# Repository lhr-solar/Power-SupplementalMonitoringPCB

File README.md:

# Power-SupplementalMonitoringPCB

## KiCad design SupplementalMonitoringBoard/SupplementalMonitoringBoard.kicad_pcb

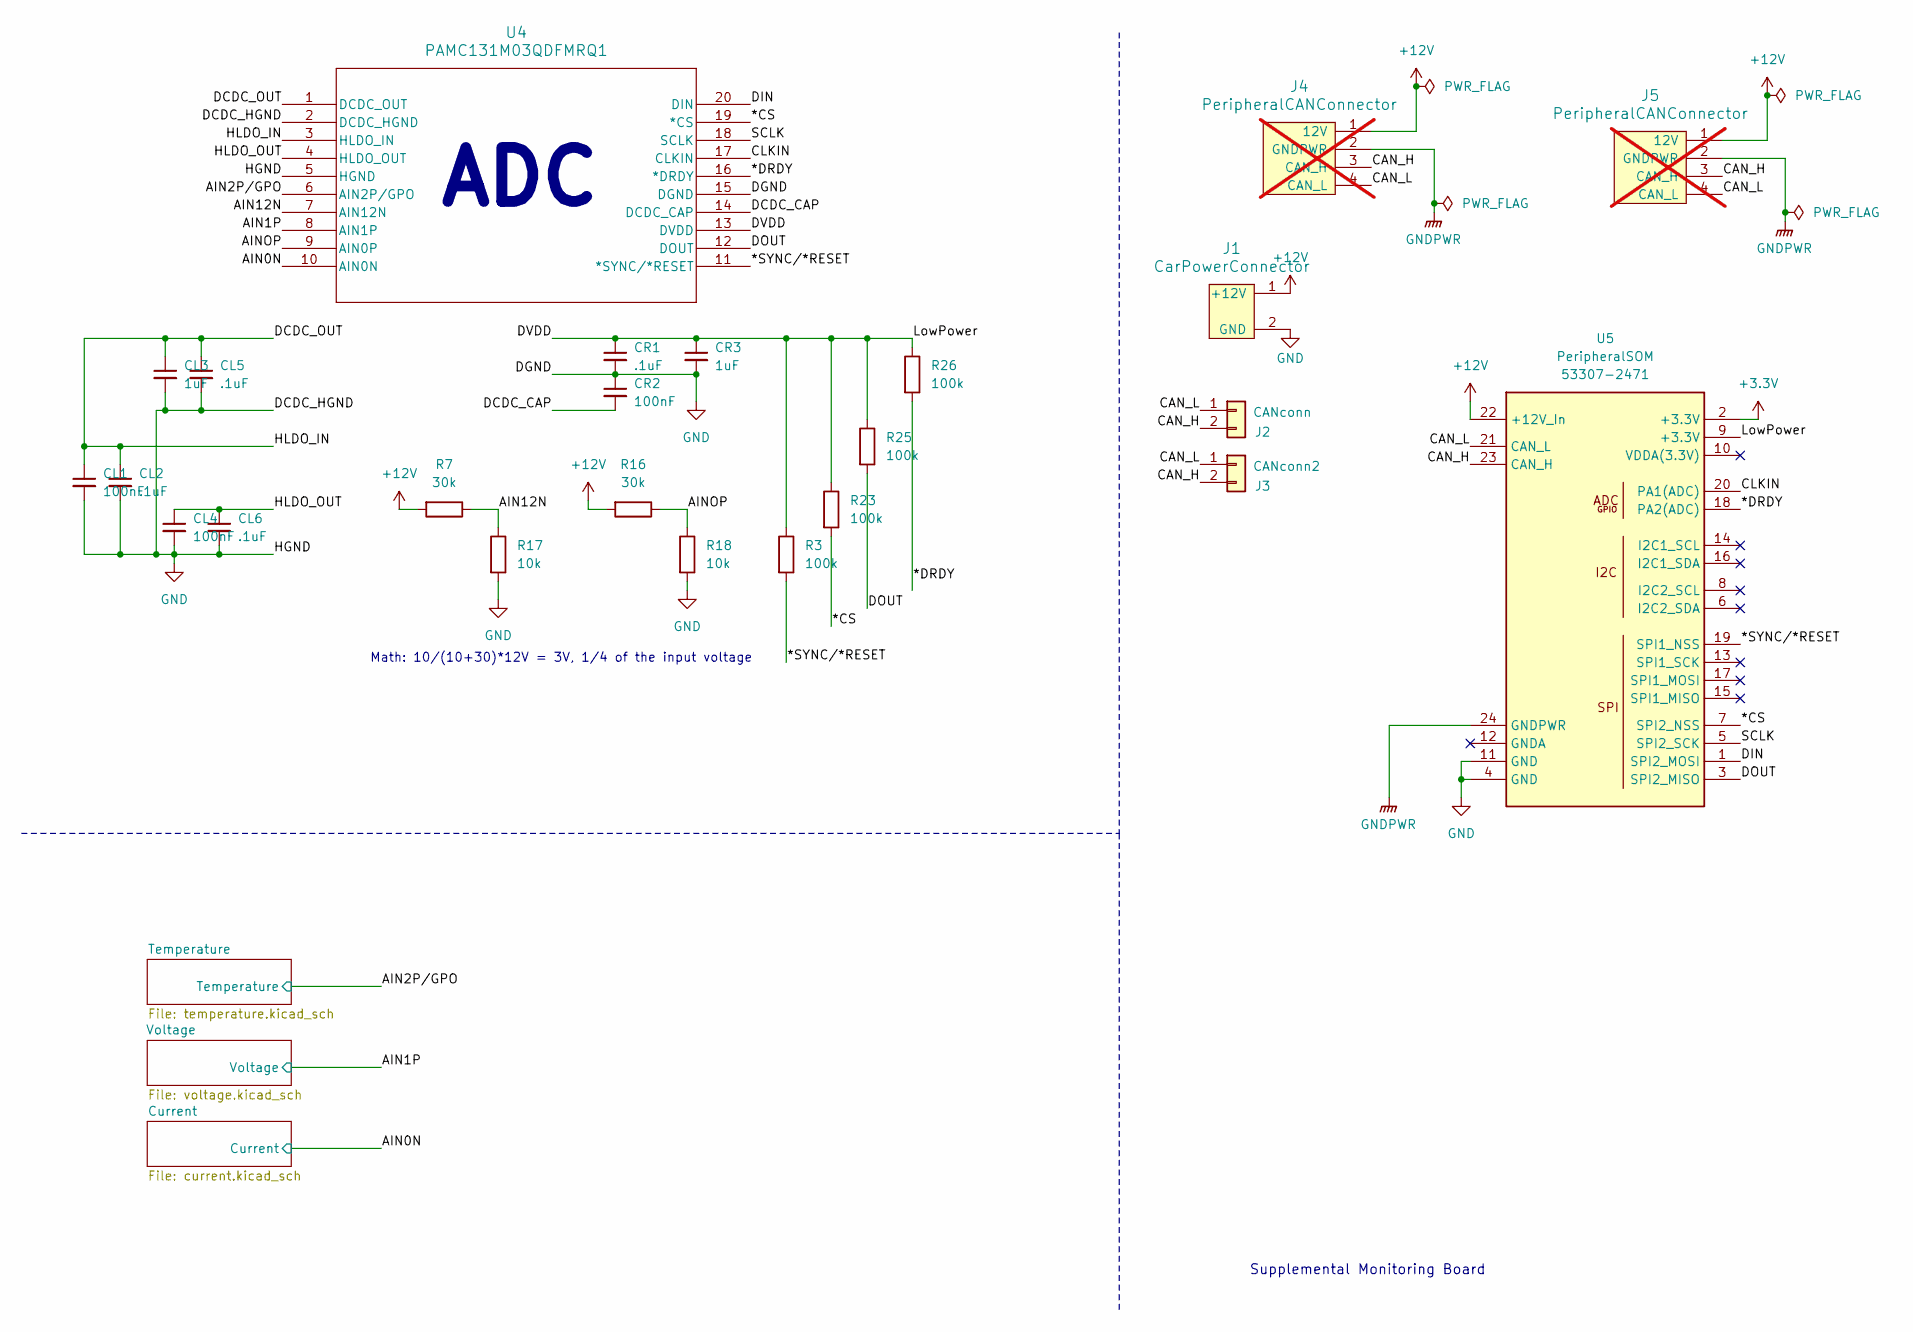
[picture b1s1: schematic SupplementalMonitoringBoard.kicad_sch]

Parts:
CL1, CL4: 100nF; C_0805_2012Metric
CL2, CL5, CL6: .1uF; C_0805_2012Metric
CL3: 1uF; C_0805_2012Metric
CR1: .1uF; C_0805_2012Metric
CR2: 100nF; C_0805_2012Metric
CR3: 1uF; C_0805_2012Metric
J1: CarPowerConnector; Molex_Micro-Fit_3.0_43650-0215_1x02_P3.00mm_Vertical
J2: CANconn; Molex_Micro-Fit_3.0_43650-0215_1x02_P3.00mm_Vertical
J3: CANconn2; Molex_Micro-Fit_3.0_43650-0215_1x02_P3.00mm_Vertical
J4, J5: PeripheralCANConnector; Molex_MicroFit3.0_1x4xP3.00mm_PolarizingPeg_Vertical; not fitted
R3, R23, R25, R26: 100k; R_0805_2012Metric
R7, R16: 30k; R_0805_2012Metric
R17, R18: 10k; R_0805_2012Metric
U4: PAMC131M03QDFMRQ1; SOIC20_DFM_TEX
U5: PeripheralSOM

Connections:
+3.3V: U5.2 (+3.3V); also elsewhere on the board
+12V: J1.1 (+12V), J4.1 (12V), J5.1 (12V), R7.2, R16.2, U5.22 (+12V_In); also elsewhere on the board
/*CS: R23.2, U4.19 (*CS), U5.7 (SPI2_NSS)
/*DRDY: R26.2, U4.16 (*DRDY), U5.18 (PA2(ADC))
/*SYNC/*RESET: R3.2, U4.11 (*SYNC/*RESET), U5.19 (SPI1_NSS)
/AIN0N: U4.10 (AIN0N); also elsewhere on the board
/AIN1P: U4.8 (AIN1P); also elsewhere on the board
/AIN2P/GPO: U4.6 (AIN2P/GPO); also elsewhere on the board
/AIN12N: R7.1, R17.1, U4.7 (AIN12N)
/AINOP: R16.1, R18.1, U4.9 (AIN0P)
/CAN_H: J2.2, J3.2, J4.3 (CAN_H), J5.3 (CAN_H), U5.23 (CAN_H)
/CAN_L: J2.1, J3.1, J4.4 (CAN_L), J5.4 (CAN_L), U5.21 (CAN_L)
/CLKIN: U4.17 (CLKIN), U5.20 (PA1(ADC))
/DCDC_CAP: CR2.2, U4.14 (DCDC_CAP)
/DCDC_OUT: CL1.1, CL2.1, CL3.1, CL5.1, U4.1 (DCDC_OUT), U4.3 (HLDO_IN)
/DIN: U4.20 (DIN), U5.1 (SPI2_MOSI)
/DOUT: R25.2, U4.12 (DOUT), U5.3 (SPI2_MISO)
/DVDD: CR1.1, CR3.1, R3.1, R23.1, R25.1, R26.1, U4.13 (DVDD), U5.9 (+3.3V)
/HLDO_OUT: CL4.1, CL6.1, U4.4 (HLDO_OUT)
/SCLK: U4.18 (SCLK), U5.5 (SPI2_SCK)
GND: CL1.2, CL2.2, CL3.2, CL4.2, CL5.2, CL6.2, CR1.2, CR2.1, CR3.2, J1.2 (GND), R17.2, R18.2, U4.2 (DCDC_HGND), U4.5 (HGND), U4.15 (DGND), U5.4 (GND), U5.11 (GND); also elsewhere on the board
GNDPWR: J4.2 (GNDPWR), J5.2 (GNDPWR), U5.24 (GNDPWR)

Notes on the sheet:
ADC
Math: 10/(10+30)*12V = 3V, 1/4 of the input voltage
ADC
Supplemental Monitoring Board

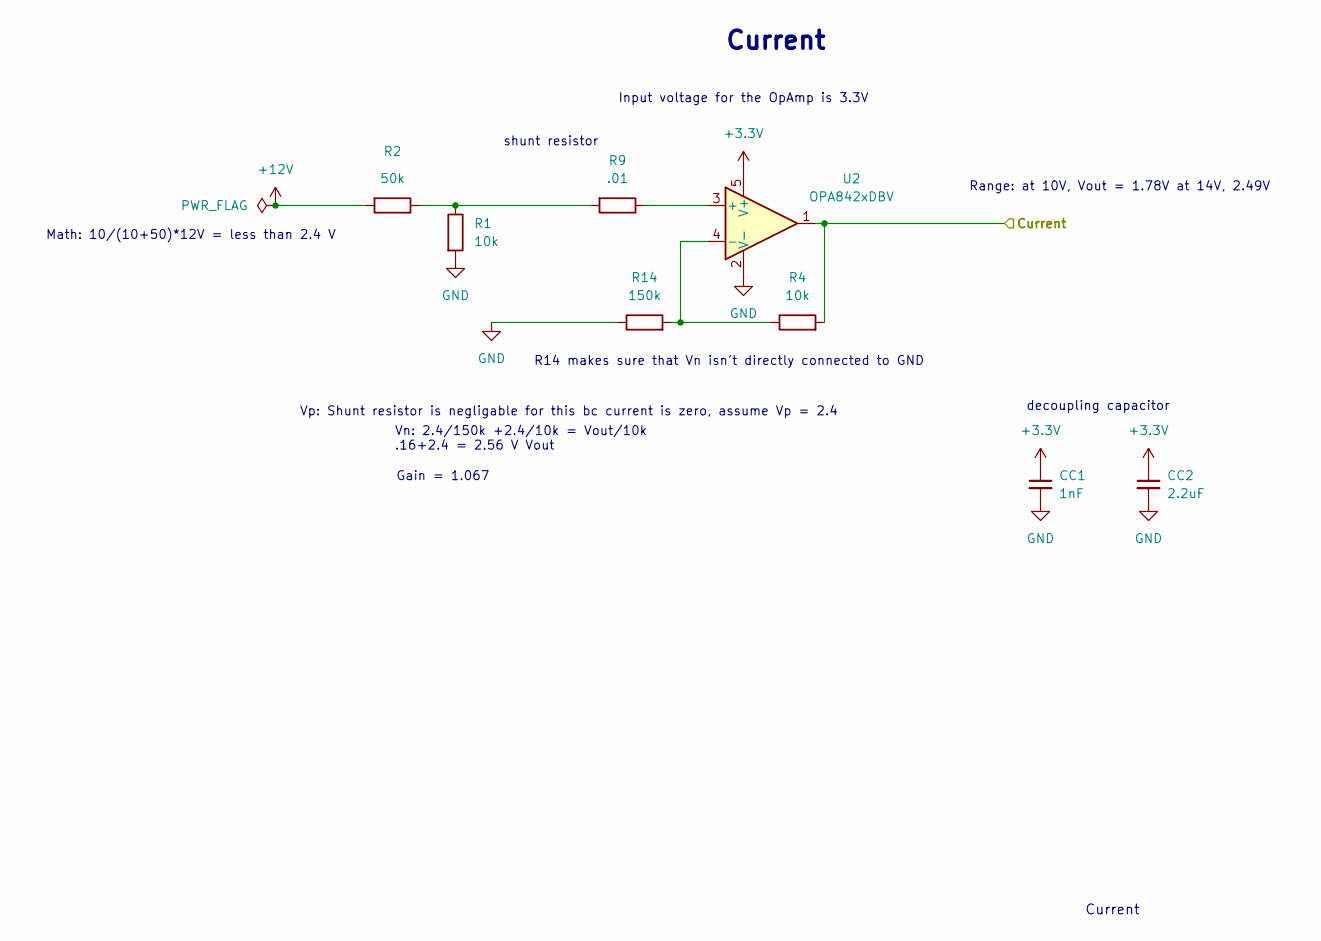
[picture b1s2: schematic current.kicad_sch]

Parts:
CC1: 1nF; C_0805_2012Metric
CC2: 2.2uF; C_0805_2012Metric
R1, R4: 10k; R_0805_2012Metric
R2: 50k; R_0805_2012Metric
R9: .01; R_0805_2012Metric
R14: 150k; R_0805_2012Metric
U2: OPA842xDBV; SOT-23-5

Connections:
+3.3V: CC1.1, CC2.1, U2.5 (V+); also elsewhere on the board
+12V: R2.2; also elsewhere on the board
/AIN0N: R4.2, U2.1; also elsewhere on the board
GND: CC1.2, CC2.2, R1.2, R14.1, U2.2 (V-); also elsewhere on the board
unnamed: R1.1, R2.1, R9.2
unnamed: R9.1, U2.3 (+)
unnamed: R4.1, R14.2, U2.4 (-)

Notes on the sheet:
Current
shunt resistor
Vn: 2.4/150k +2.4/10k = Vout/10k .16+2.4 = 2.56 V Vout
Input voltage for the OpAmp is 3.3V
Math: 10/(10+50)*12V = less than 2.4 V
Gain = 1.067
decoupling capacitor
Vp: Shunt resistor is negligable for this bc current is zero, assume Vp = 2.4
R14 makes sure that Vn isn't directly connected to GND
Range: at 10V, Vout = 1.78V at 14V, 2.49V

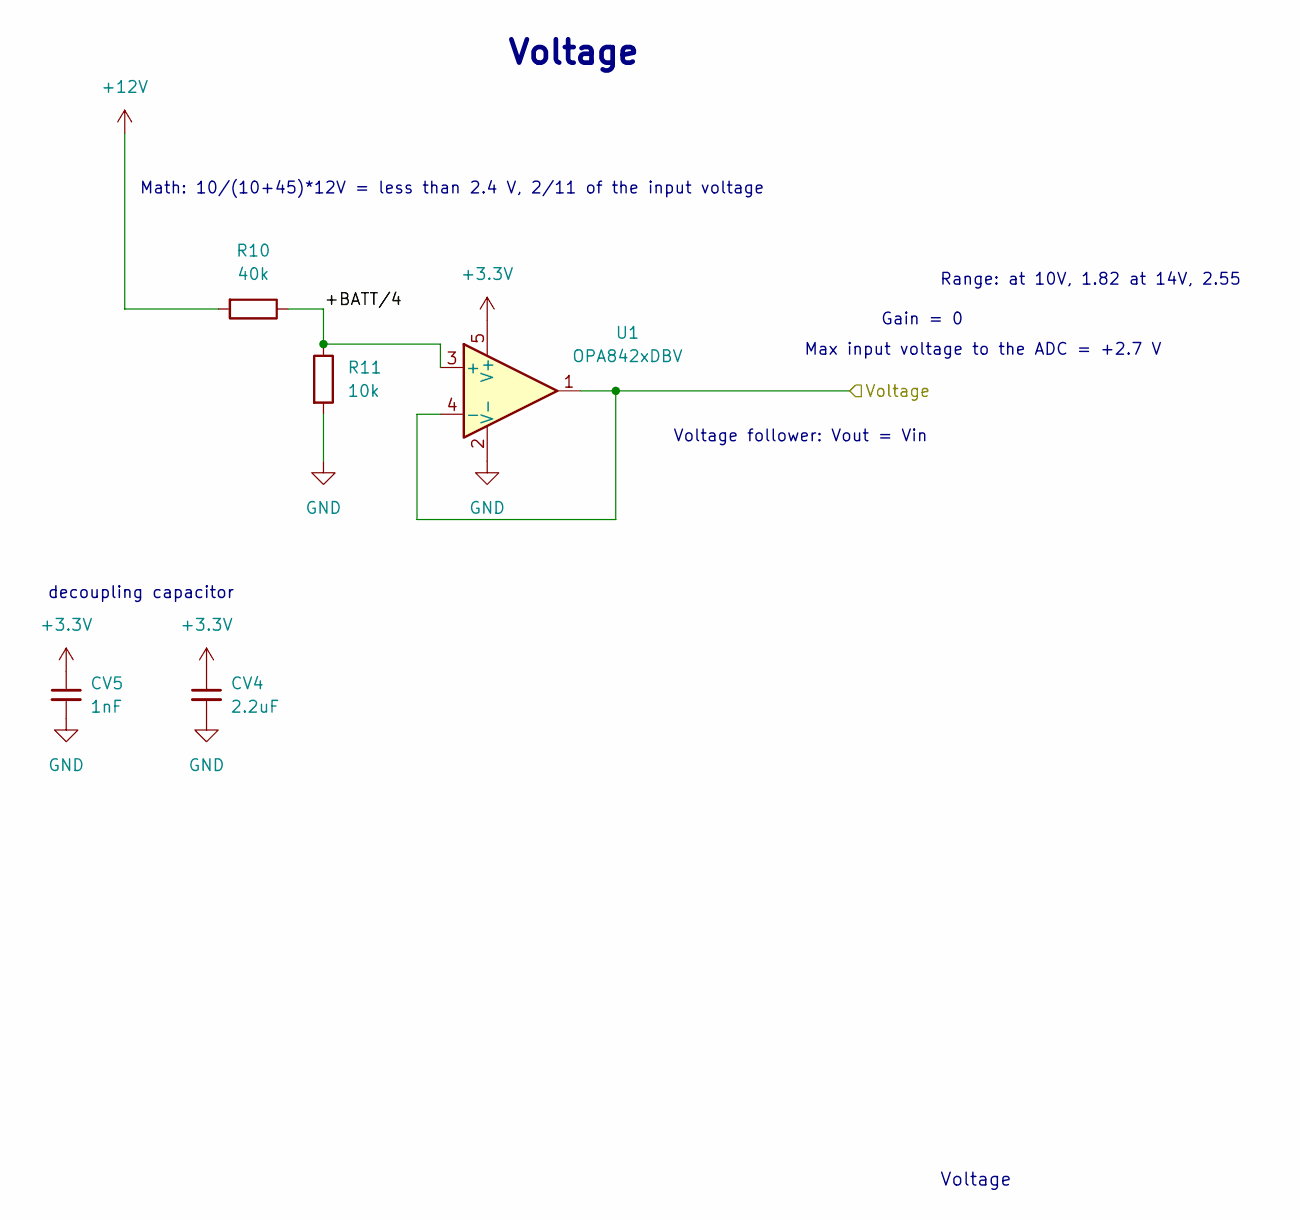
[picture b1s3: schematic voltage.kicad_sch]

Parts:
CV4: 2.2uF; C_0805_2012Metric
CV5: 1nF; C_0805_2012Metric
R10: 40k; R_0805_2012Metric
R11: 10k; R_0805_2012Metric
U1: OPA842xDBV; SOT-23-5

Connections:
+3.3V: CV4.1, CV5.1, U1.5 (V+); also elsewhere on the board
+12V: R10.2; also elsewhere on the board
/AIN1P: U1.1, U1.4 (-); also elsewhere on the board
/Voltage/+BATT/4: R10.1, R11.1, U1.3 (+)
GND: CV4.2, CV5.2, R11.2, U1.2 (V-); also elsewhere on the board

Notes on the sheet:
Max input voltage to the ADC = +2.7 V
Voltage
Voltage follower: Vout = Vin
Math: 10/(10+45)*12V = less than 2.4 V, 2/11 of the input voltage
Gain = 0
Range: at 10V, 1.82 at 14V, 2.55
decoupling capacitor

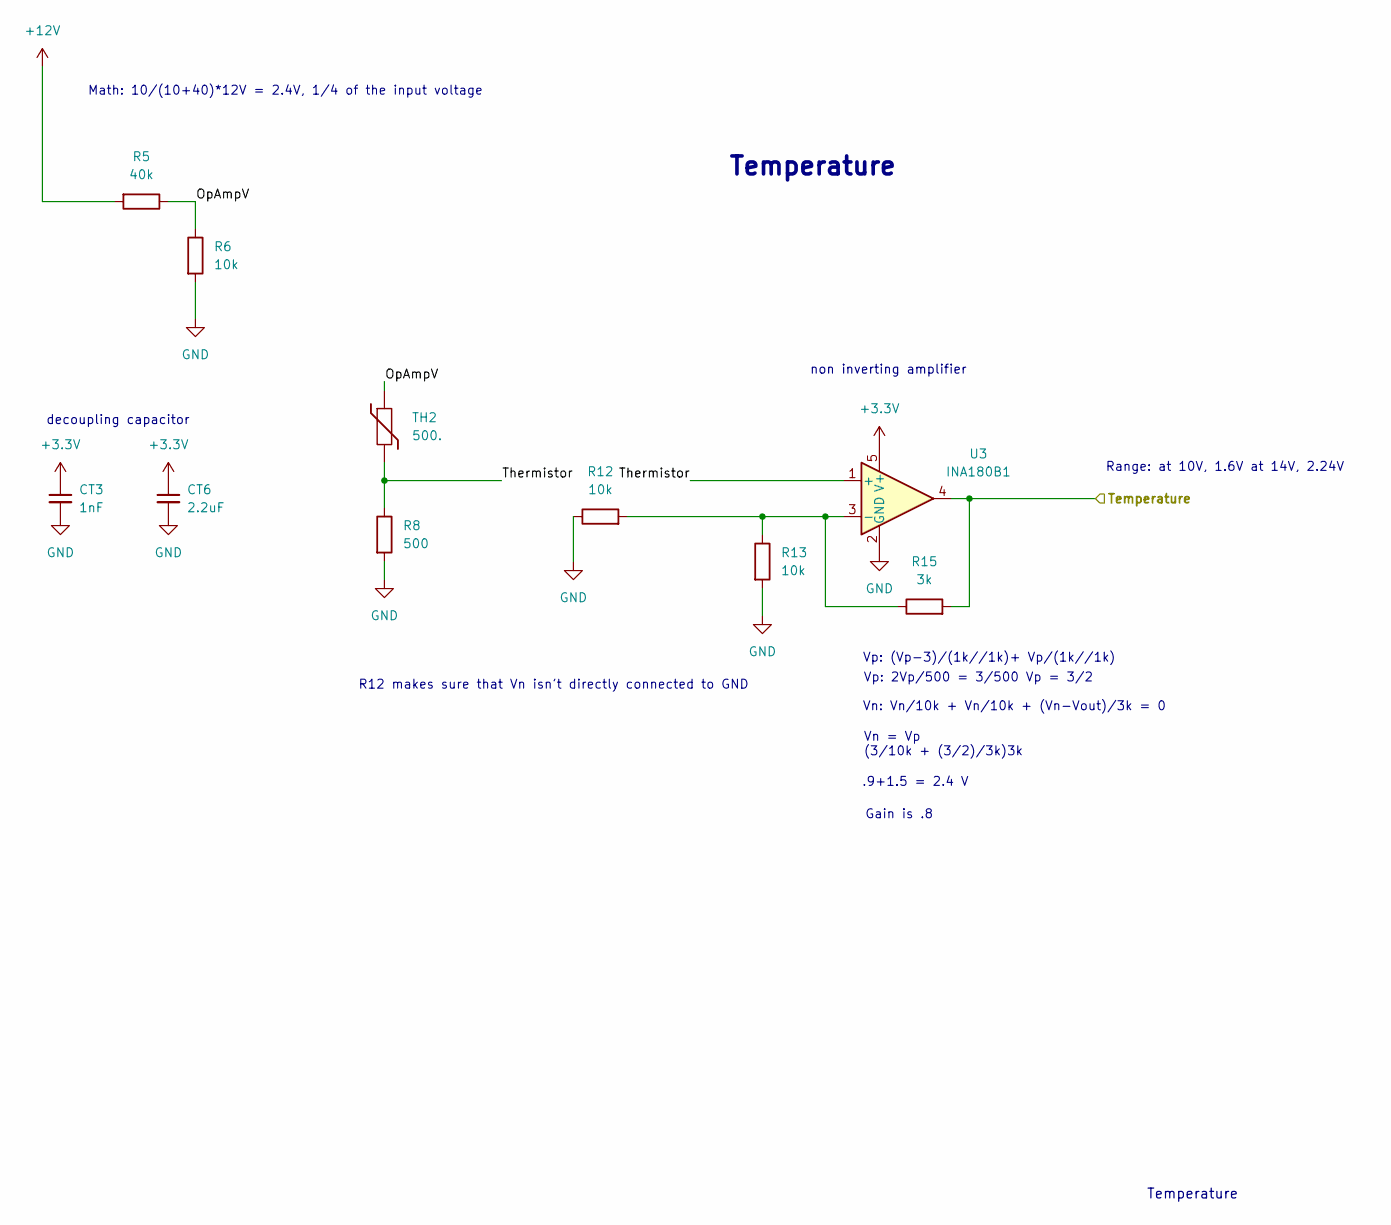
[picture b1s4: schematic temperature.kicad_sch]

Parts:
CT3: 1nF; C_0805_2012Metric
CT6: 2.2uF; C_0805_2012Metric
R5: 40k; R_0805_2012Metric
R6, R12, R13: 10k; R_0805_2012Metric
R8: 500; R_0805_2012Metric
R15: 3k; R_0805_2012Metric
TH2: 500.; R_0805_2012Metric
U3: INA180B1; SOT-23-5

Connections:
+3.3V: CT3.1, CT6.1, U3.5 (V+); also elsewhere on the board
+12V: R5.2; also elsewhere on the board
/AIN2P/GPO: R15.2, U3.4; also elsewhere on the board
/Temperature/OpAmpV: R5.1, R6.1, TH2.1
/Temperature/Thermistor: R8.1, TH2.2, U3.1 (+)
GND: CT3.2, CT6.2, R6.2, R8.2, R12.1, R13.2, U3.2 (GND); also elsewhere on the board
unnamed: R12.2, R13.1, R15.1, U3.3 (-)

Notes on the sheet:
Vn = Vp (3/10k + (3/2)/3k)3k
non inverting amplifier
Range: at 10V, 1.6V at 14V, 2.24V
.9+1.5 = 2.4 V
Vn: Vn/10k + Vn/10k + (Vn-Vout)/3k = 0
Math: 10/(10+40)*12V = 2.4V, 1/4 of the input voltage
decoupling capacitor
Vp: 2Vp/500 = 3/500 Vp = 3/2
Temperature
Vp: (Vp-3)/(1k//1k)+ Vp/(1k//1k)
R12 makes sure that Vn isn't directly connected to GND
Gain is .8

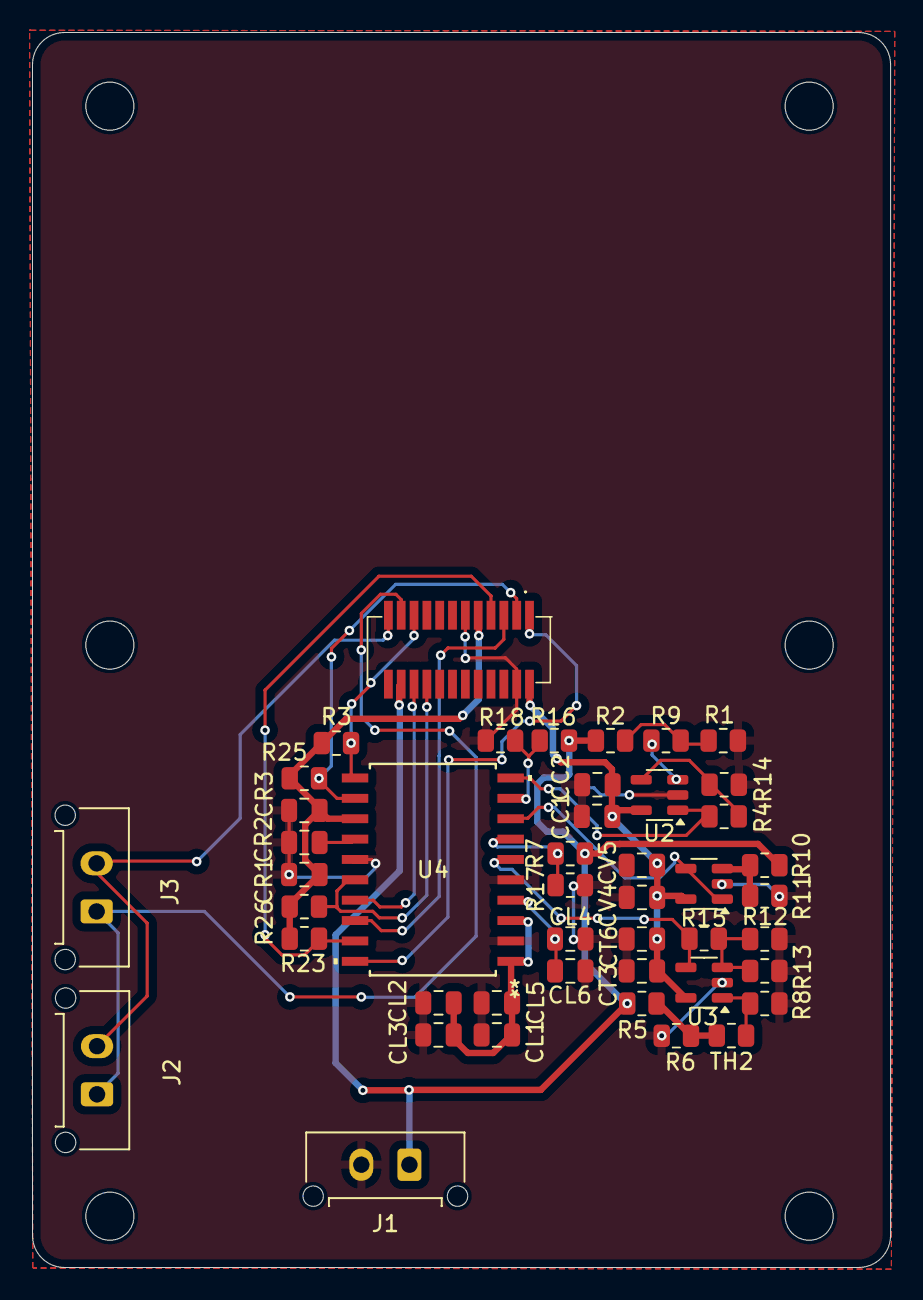
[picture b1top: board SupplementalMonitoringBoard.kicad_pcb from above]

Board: 2 copper layers, 53.5 x 77.0 mm, 45 parts (0 on the bottom side), 28 nets.

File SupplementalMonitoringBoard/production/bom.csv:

Designator,Footprint,Quantity,Value,LCSC Part #
"_2, ",,2,,
"CC1, CT3, CV5",0805,3,1nF,
"CC2, CT6, CV4",0805,3,2.2uF,
"CL1, CL4, CR2",0805,3,100nF,
"CL2, CL5, CL6, CR1",0805,4,.1uF,
"CL3, CR3",0805,2,1uF,
J1,Molex_Micro-Fit_3.0_43650-0215_1x02_P3.00mm_Vertical,1,CarPowerConnector,
J2,Molex_Micro-Fit_3.0_43650-0215_1x02_P3.00mm_Vertical,1,CANconn,
J3,Molex_Micro-Fit_3.0_43650-0215_1x02_P3.00mm_Vertical,1,CANconn2,
"R1, R11, R12, R13, R17, R18, R4, R6",0805,8,10k,
"R10, R5",0805,2,40k,
R14,0805,1,150k,
R15,0805,1,3k,
"R16, R7",0805,2,30k,
R2,0805,1,50k,
"R23, R25, R26, R3",0805,4,100k,
R8,0805,1,500,
R9,0805,1,.01,
TH2,0805,1,500.,
"U1, U2",SOT-23-5,2,OPA842xDBV,
U3,SOT-23-5,1,INA180B1,
U4,SOIC20_DFM_TEX,1,PAMC131M03QDFMRQ1,
U5,PeripheralSOM,1,PeripheralSOM,

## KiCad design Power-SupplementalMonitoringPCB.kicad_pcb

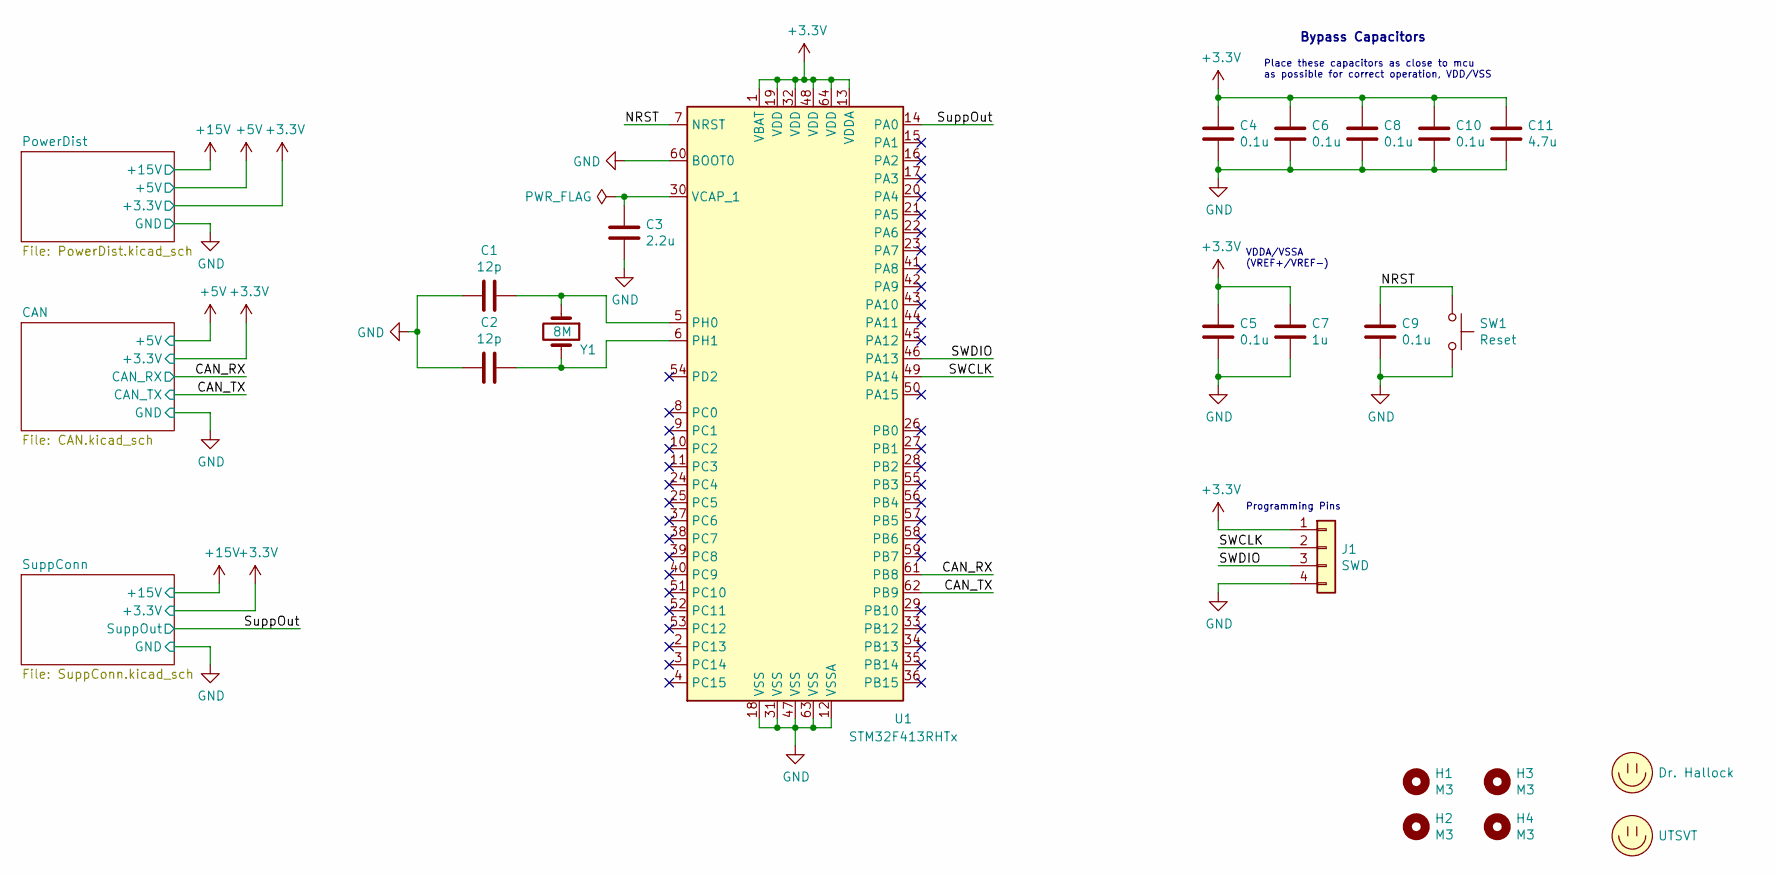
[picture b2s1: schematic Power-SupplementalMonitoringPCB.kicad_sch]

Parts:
C1, C2: 12p; C_0805_2012Metric
C3: 2.2u; C_0805_2012Metric
C4, C5, C6, C8, C9, C10: 0.1u; C_0805_2012Metric
C7: 1u; C_0805_2012Metric
C11: 4.7u; C_0805_2012Metric
H1, H2, H3, H4: M3; MountingHole_3mm
J1: SWD; PinHeader_1x04_P2.54mm_Vertical
LOGO1: Dr. Hallock; Hallock_Image_Tiny
LOGO2: UTSVT; UTSVT_Logo_Symbol
SW1: Reset; SW_SPST_B3SL-1002P
U1: STM32F413RHTx; LQFP-64_10x10mm_P0.5mm
Y1: 8M; Crystal_SMD_TXC_7A-2Pin_5x3.2mm

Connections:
+3V3: C4.1, C5.1, C6.1, C7.1, C8.1, C10.1, C11.1, J1.1, U1.1 (VBAT), U1.13 (VDDA), U1.19 (VDD), U1.32 (VDD), U1.48 (VDD), U1.64 (VDD); also elsewhere on the board
/CAN_RX: U1.61 (PB8); also elsewhere on the board
/CAN_TX: U1.62 (PB9); also elsewhere on the board
/NRST: C9.1, SW1.1, U1.7 (NRST)
/SWCLK: J1.2, U1.49 (PA14)
/SWDIO: J1.3, U1.46 (PA13)
/SuppOut: U1.14 (PA0); also elsewhere on the board
GND: C1.2, C2.2, C3.2, C4.2, C5.2, C6.2, C7.2, C8.2, C9.2, C10.2, C11.2, J1.4, SW1.2, U1.12 (VSSA), U1.18 (VSS), U1.31 (VSS), U1.47 (VSS), U1.60 (BOOT0), U1.63 (VSS); also elsewhere on the board
unnamed: C1.1, U1.5 (PH0), Y1.1
unnamed: C2.1, U1.6 (PH1), Y1.2
unnamed: C3.1, U1.30 (VCAP_1)

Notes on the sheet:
Programming Pins
Place these capacitors as close to mcu as possible for correct operation, VDD/VSS
Bypass Capacitors
VDDA/VSSA (VREF+/VREF-)

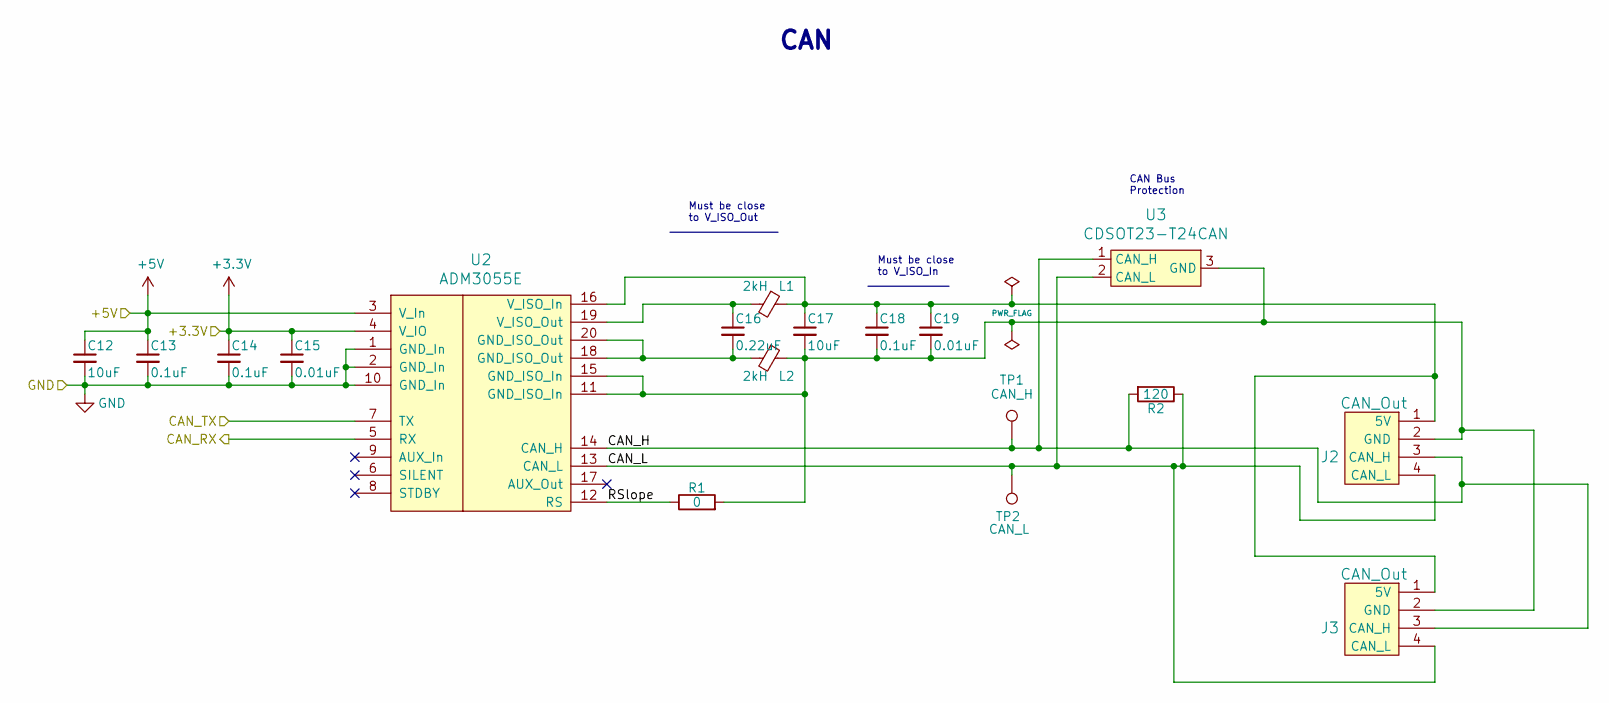
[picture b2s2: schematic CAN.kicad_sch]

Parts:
C12, C17: 10uF; C_0805_2012Metric
C13, C14, C18: 0.1uF; C_0805_2012Metric
C15, C19: 0.01uF; C_0805_2012Metric
C16: 0.22uF; C_0805_2012Metric
J2, J3: CAN_Out; Molex_MicroFit3.0_1x4xP3.00mm_PolarizingPeg_Vertical
L1, L2: 2kH; L_0805_2012Metric
R1: 0; R_0805_2012Metric
R2: 120; R_0805_2012Metric
TP1: CAN_H; TestPoint_Keystone_5005-5009_Compact
TP2: CAN_L; TestPoint_Keystone_5005-5009_Compact
U2: ADM3055E; SOIC-20W_7.5x15.4mm_Pitch1.27mm
U3: CDSOT23-T24CAN; SOT-23W

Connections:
+3V3: C14.1, C15.1, U2.4 (V_IO); also elsewhere on the board
+5V: C12.1, C13.1, U2.3 (V_In); also elsewhere on the board
/CAN/CAN_H: J2.3 (CAN_H), J3.3 (CAN_H), R2.2, TP1.1, U2.14 (CAN_H), U3.1 (CAN_H)
/CAN/CAN_L: J2.4 (CAN_L), J3.4 (CAN_L), R2.1, TP2.1, U2.13 (CAN_L), U3.2 (CAN_L)
/CAN/RSlope: R1.1, U2.12 (RS)
/CAN_RX: U2.5 (RX); also elsewhere on the board
/CAN_TX: U2.7 (TX); also elsewhere on the board
GND: C12.2, C13.2, C14.2, C15.2, U2.1 (GND_In), U2.2 (GND_In), U2.10 (GND_In); also elsewhere on the board
unnamed: C16.1, L1.2, U2.19 (V_ISO_Out)
unnamed: C16.2, L2.2, U2.18 (GND_ISO_Out), U2.20 (GND_ISO_Out)
unnamed: C17.1, C18.1, C19.1, J2.1 (5V), J3.1 (5V), L1.1, U2.16 (V_ISO_In)
unnamed: C17.2, C18.2, C19.2, J2.2 (GND), J3.2 (GND), L2.1, R1.2, U2.11 (GND_ISO_In), U2.15 (GND_ISO_In), U3.3 (GND)

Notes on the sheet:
Must be close to V_ISO_In
Must be close to V_ISO_Out
CAN Bus Protection
CAN

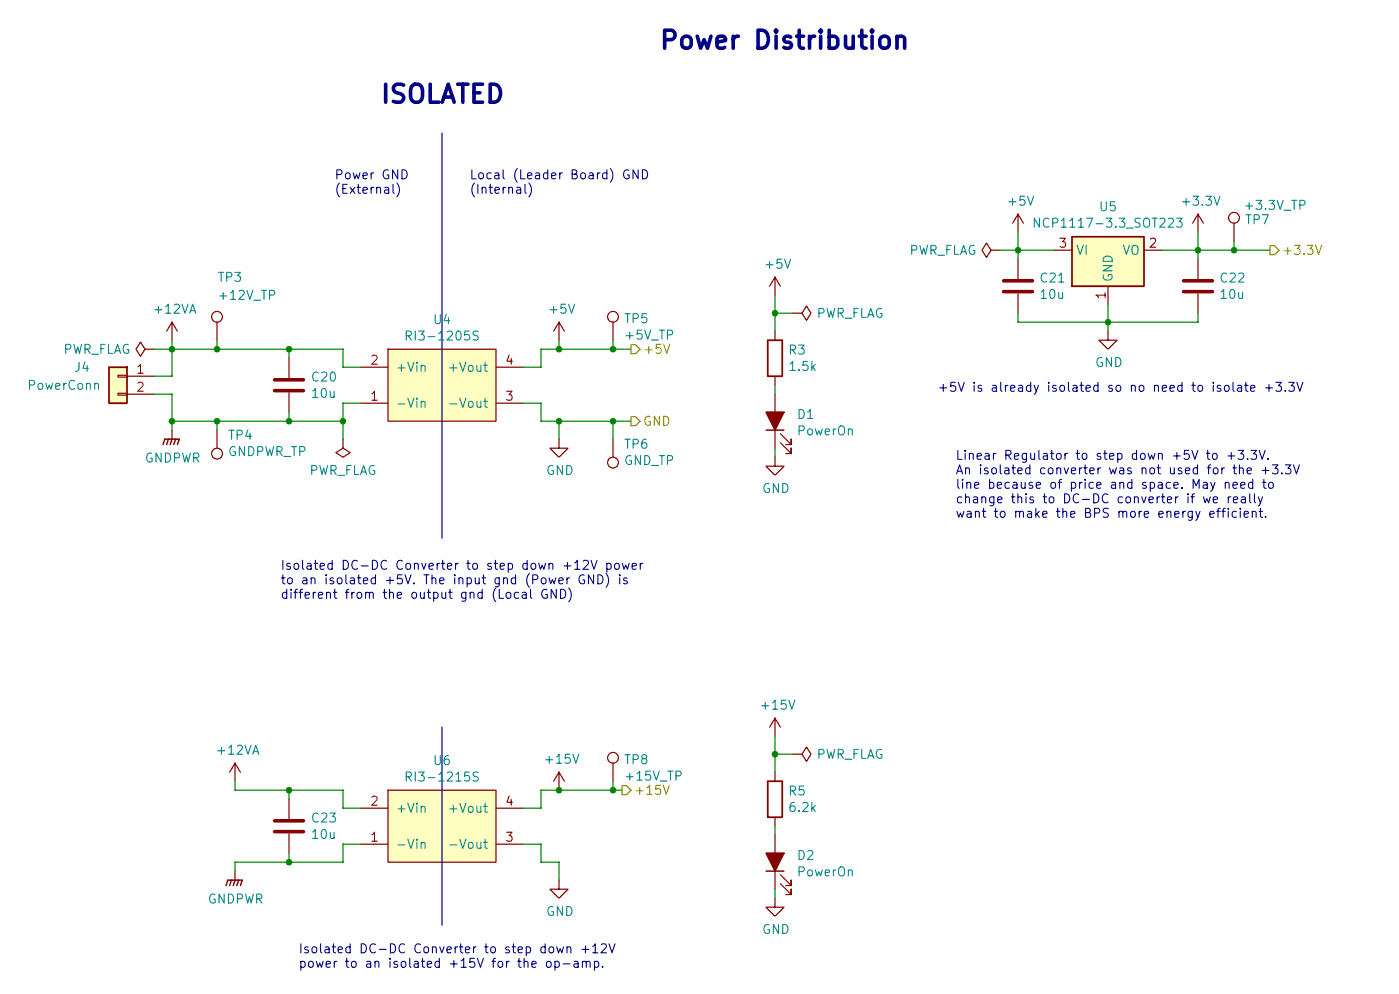
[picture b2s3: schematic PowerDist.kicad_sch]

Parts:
C20, C23: 10u; C_2220_5750Metric
C21, C22: 10u; C_0805_2012Metric
D1, D2: PowerOn; LED_0805_2012Metric
J4: PowerConn; Molex_MicroFit3.0_1x2xP3.00mm_PolarizingPeg_Vertical
R3: 1.5k; R_0805_2012Metric
R5: 6.2k; R_0805_2012Metric
TP3: +12V_TP; TestPoint_Keystone_5005-5009_Compact
TP4: GNDPWR_TP; TestPoint_Keystone_5005-5009_Compact
TP5: +5V_TP; TestPoint_Keystone_5005-5009_Compact
TP6: GND_TP; TestPoint_Keystone_5005-5009_Compact
TP7: +3.3V_TP; TestPoint_Keystone_5005-5009_Compact
TP8: +15V_TP; TestPoint_Keystone_5005-5009_Compact
U4: RI3-1205S; RI3_DC_Converter
U5: NCP1117-3.3_SOT223; SOT-223-3_TabPin2
U6: RI3-1215S; RI3_DC_Converter

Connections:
+3V3: C22.1, TP7.1, U5.2 (VO); also elsewhere on the board
+5V: C21.1, R3.1, TP5.1, U4.4 (+Vout), U5.3 (VI); also elsewhere on the board
+12VA: C20.1, C23.1, J4.1, TP3.1, U4.2 (+Vin), U6.2 (+Vin)
+15V: R5.1, TP8.1, U6.4 (+Vout); also elsewhere on the board
GND: C21.2, C22.2, D1.1 (K), D2.1 (K), TP6.1, U4.3 (-Vout), U5.1 (GND), U6.3 (-Vout); also elsewhere on the board
GNDPWR: C20.2, C23.2, J4.2, TP4.1, U4.1 (-Vin), U6.1 (-Vin)
unnamed: D1.2 (A), R3.2
unnamed: D2.2 (A), R5.2

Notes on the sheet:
Power GND (External)
Isolated DC-DC Converter to step down +12V power to an isolated +5V. The input gnd (Power GND) is different from the output gnd (Local GND)
ISOLATED
+5V is already isolated so no need to isolate +3.3V
Local (Leader Board) GND (Internal)
Power Distribution
Isolated DC-DC Converter to step down +12V power to an isolated +15V for the op-amp.
Linear Regulator to step down +5V to +3.3V. An isolated converter was not used for the +3.3V line because of price and space. May need to change this to DC-DC converter if we really want to make the BPS more energy efficient.

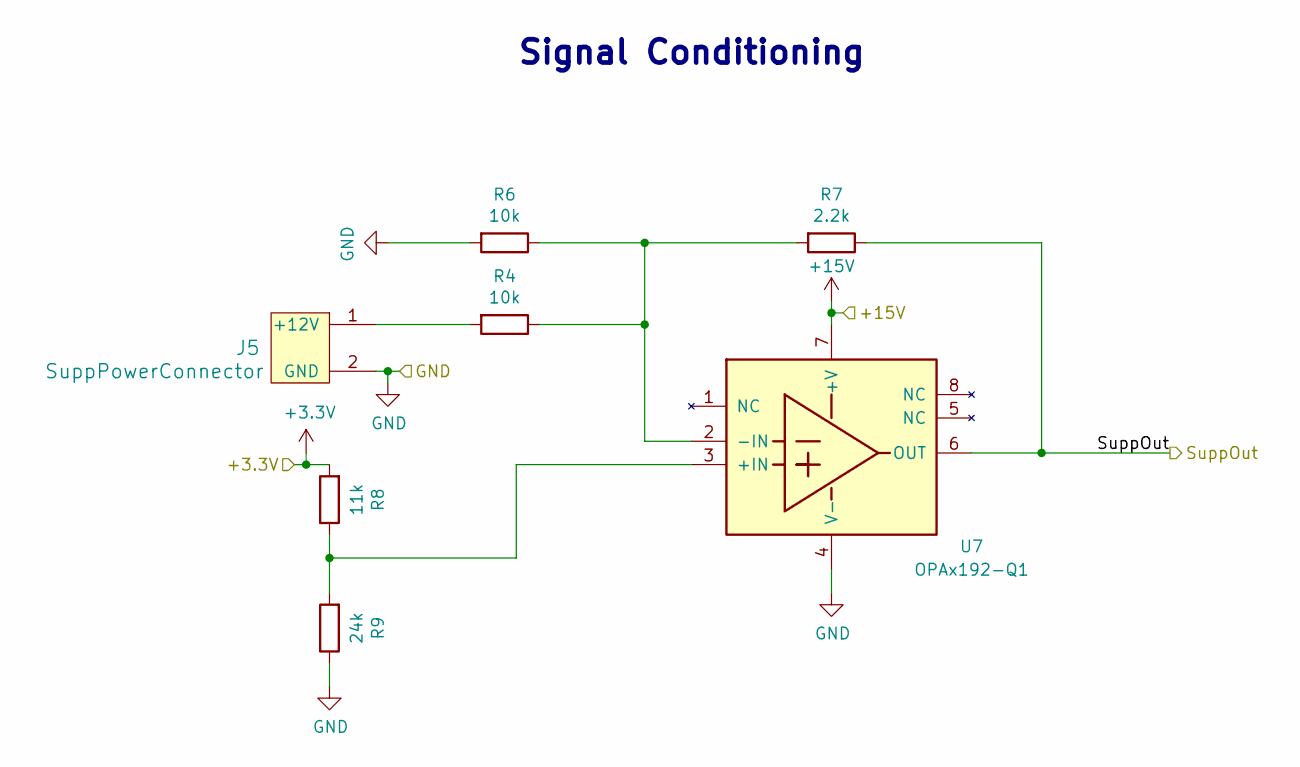
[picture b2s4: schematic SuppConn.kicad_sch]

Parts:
J5: SuppPowerConnector; Molex_MicroFit3.0_1x2xP3.00mm_PolarizingPeg_Vertical
R4, R6: 10k; R_0805_2012Metric
R7: 2.2k; R_0805_2012Metric
R8: 11k; R_0805_2012Metric
R9: 24k; R_0805_2012Metric
U7: OPAx192-Q1; VSSOP-8_3.0x3.0mm_P0.65mm

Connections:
+3V3: R8.2; also elsewhere on the board
+15V: U7.7 (+V); also elsewhere on the board
/SuppOut: R7.1, U7.6 (OUT); also elsewhere on the board
GND: J5.2 (GND), R6.2, R9.1, U7.4 (V-); also elsewhere on the board
unnamed: J5.1 (+12V), R4.2
unnamed: R4.1, R6.1, R7.2, U7.2 (-IN)
unnamed: R8.1, R9.2, U7.3 (+IN)

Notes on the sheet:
Signal Conditioning

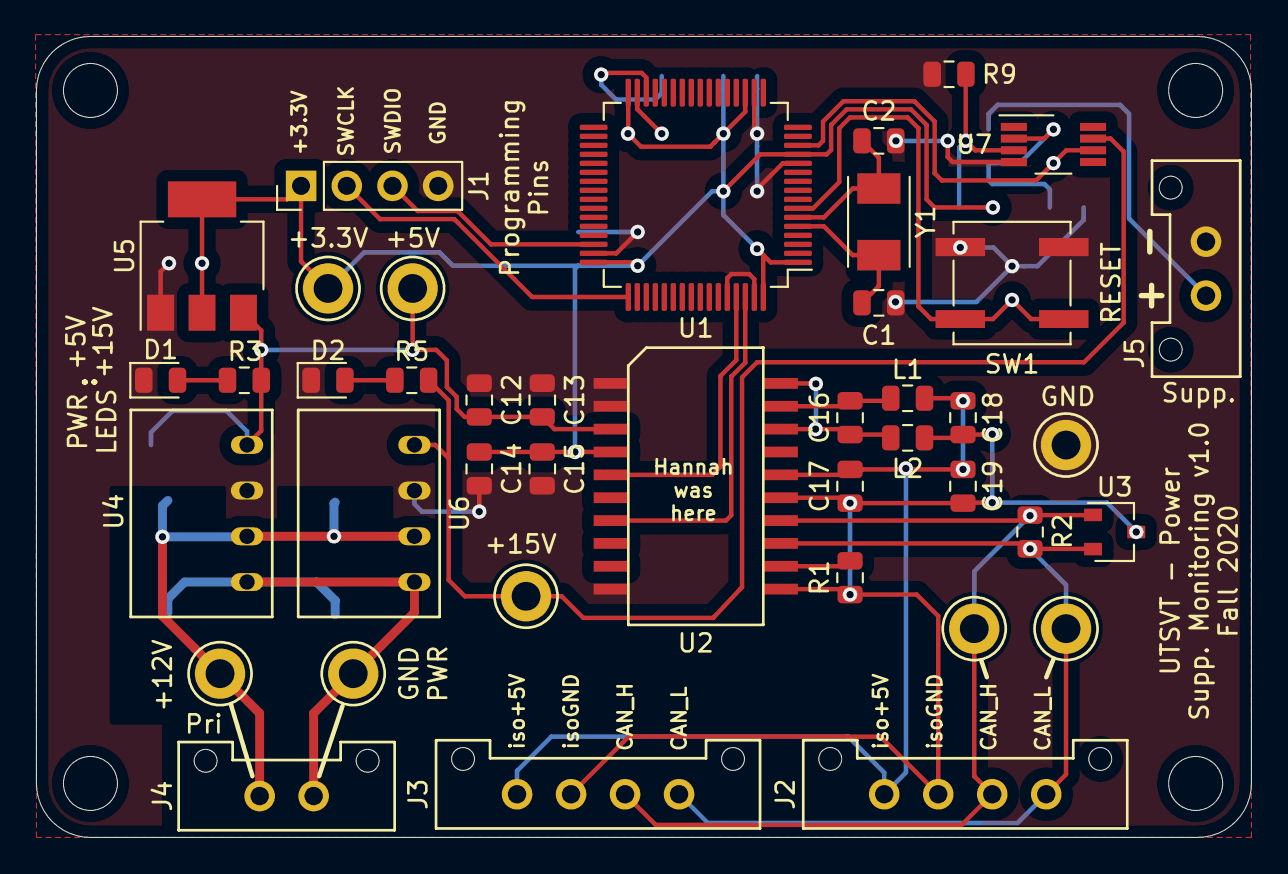
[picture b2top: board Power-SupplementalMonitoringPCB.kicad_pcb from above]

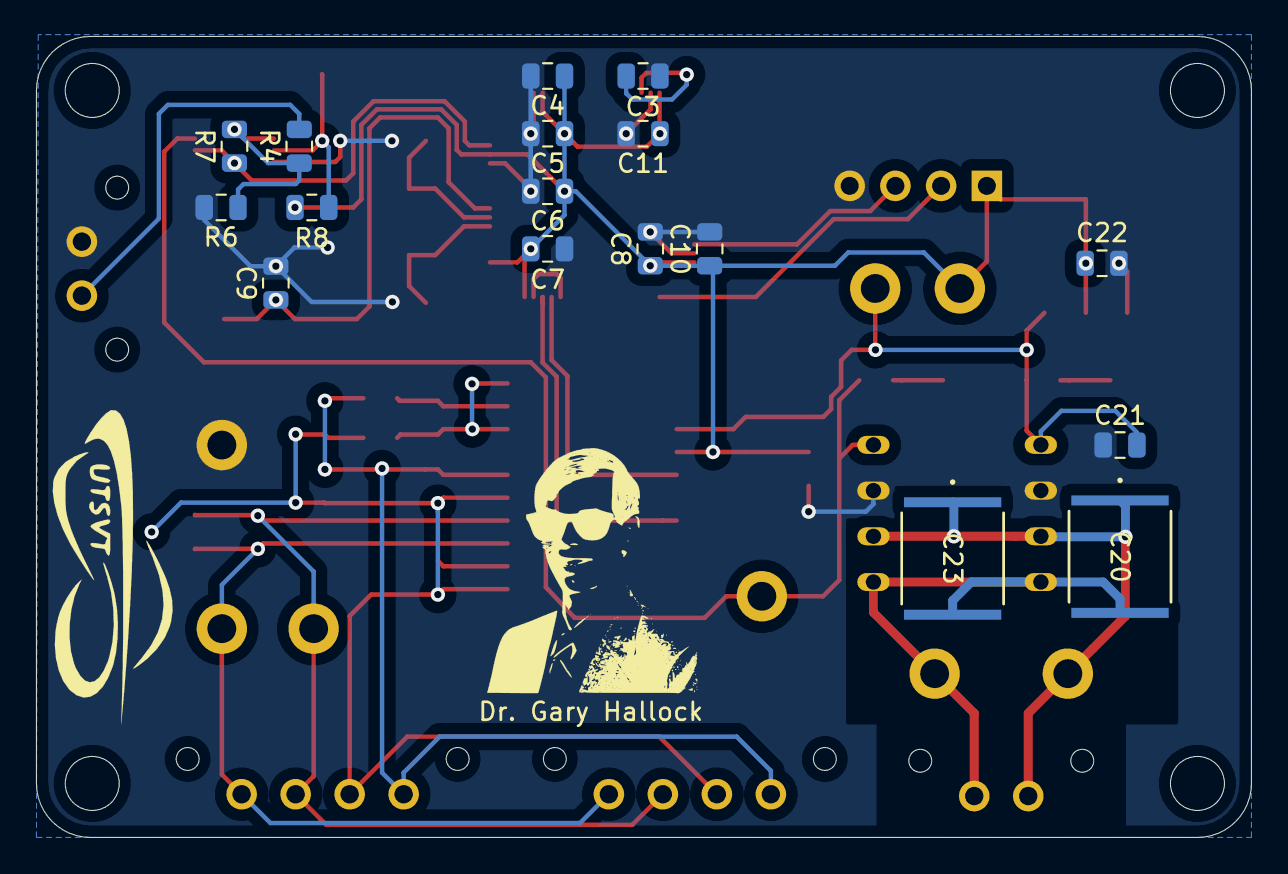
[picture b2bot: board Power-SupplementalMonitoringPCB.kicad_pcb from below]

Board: 2 copper layers, 67.5 x 44.5 mm, 64 parts (19 on the bottom side), 27 nets.

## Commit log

2020-11-21 Adds hierarchical sheets, picks PC0 for ADC
    Adds CAN & power distribution sheets. The VoltageDivision sheet is probably not needed (it uses the TPS3711 IC as a voltage comparator). PC0 is picked to be the ADC input (but we probably won't use t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
2020-11-30 Adds programming pins, bypass capacitors, & op amp
    VoltageDivision.sch now uses OPA2990 to attenuate the supplemental battery signal by ~4. Timing crystal, NRST, bypass capacitors, & SWDIO & SWCLK connections added in.
2020-11-30 Adds symbol for OPA2990
2020-11-30 Added power flags
2020-11-30 Adds project file
2020-12-05 Adds common library
2020-12-05 Lays out schematic and PCB of v1.0
2020-12-18 Makes edits from critical design review
2020-12-18 Fixes issue with the submodule
2020-12-19 Edits opamp circuitry to just one opamp and adds keepout zone under 12V and GNDPWR
2020-12-19 Correct op amp voltage measurement circuitry
2020-12-19 Fixes opamp circuitry
2020-12-20 Updates submodule
2021-01-10 Adds gerbers
2021-01-23 ads 3D models
2021-09-04 fix kicad libraries
2023-06-17 Removed submodule
2023-09-02 added UTSVT-KiCADLibraries as a submodule, updated PCB and main schematic to KiCAD 7.0
2024-11-02 Supplemental Monitoring Board
2024-11-02 Supplemental Monitioring Board v2
2024-11-02 Supplemental Monitoring Board Changes
2024-11-09 thing
2024-11-16 Adressed Reviews - Supplemental Monitoring Board
2024-11-20 PCB Layout - Supplemental Monitoring Board
2024-12-07 Supplemental Monitoring Board - Layout
2025-01-17 Supplemental_Monitoring_Board
2025-01-18 Adressed Reviews

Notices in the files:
parts and their libraries:
Copyright 2016 Accelerated Designs. All rights reserved.
